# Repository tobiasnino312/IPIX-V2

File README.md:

# IPIX-V2
Robot seguidor de línea utilizado desde el 30/08/2025 en el interzonal de Trelew de la LNR argentina con un 3° puesto interzonal. 
El mismo trabaja con el microcontrolador Arduino Nano, TB6612FNG, motores ProFast de 4000rpm, una bateria LiPo 4s 600mAh armada casera, llantas y cubiertas JSUMO SLT20 y una regleta de sensores QTR8A genérica, similar a la de Pololu. 
Posee un switch DIP para selección de estrategias o configuraciones (empleado para cambio de velocidad según interior o exterior de la pista) y una programación basada en PID básico. 
En cuanto al código, se probó un sistema con intervalos de tiempo para el control dinámico de velocidades base/máximas o parámetros de cálculo del PID, pero debido al poco tiempo de pruebas en pista no se pudo aprovechar. Además, se está desarrollando un algoritmo con Twiddle (un algoritmo de tuning de PID con una especie de aprendizaje escalonado muy básico) que aún no fue probado en pista, con el objetivo de optimizar el tiempo de pruebas en competencia y recopilar datos de tiempo de vuelta y constantes del cálculo del PID.
Por otro lado, se está avanzando con el diseño de una tercera versión (IPIX V3) migrando a una BluePill (STM32F103C8T6), RZ7899 como drivers de motores, hueco para una turbina para mayor adherencia (la limitante actual del prototipo) y 10 sensores QRE1113 directamente soldados a placa con lectura directa por cada canal del ADC disponible.

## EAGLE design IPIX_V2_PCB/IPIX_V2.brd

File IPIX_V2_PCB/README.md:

Todos los diseños realizados en esta segunda versión del robot fueron realizados en Eagle 7.6.0

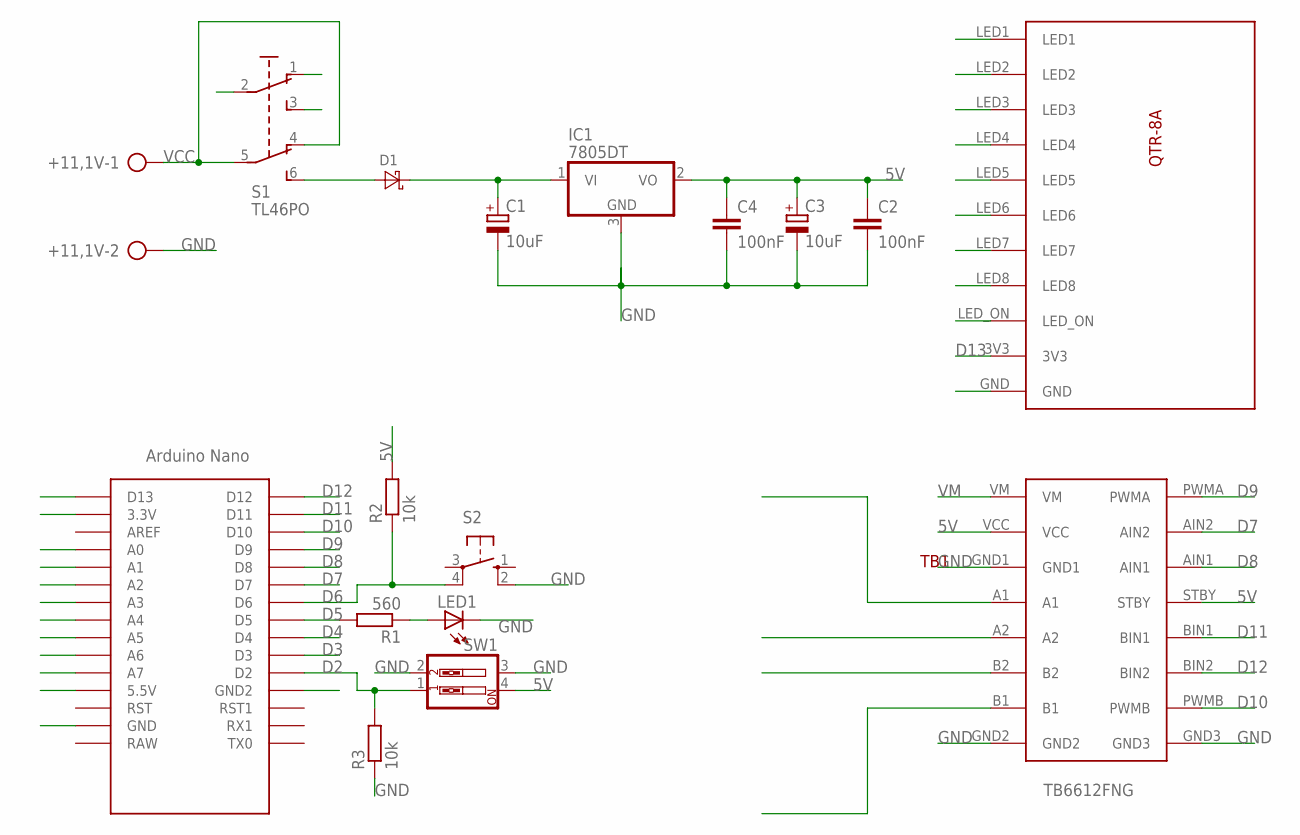
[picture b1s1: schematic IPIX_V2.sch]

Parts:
+11,1V: AK500/2-H
C1, C3: 10uF; E2,5-6E
C2, C4: 100nF; C0805
D1: DIODE-SCHOTTKY-DO201AD; DO201AD
IC1: 7805DT; TO252
LED1: LED3MM
R1: 560; 0204/7
R2, R3: 10k; R0805
S1: TL46PO; TL4XPO
S2: 10-XX; B3F-10XX
SW1: SW_DIP-2; EDG-02
TB1: TB6612FNG
U$1: NANO
U$2: QTR-8A

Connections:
3,3V: U$1.3.3V
5V: C2.1, C3.+, C4.1, IC1.2 (VO), R2.2, SW1.4, TB1.STBY, TB1.VCC, U$1.5V (5.5V), U$2.LED8
A0: U$1.A0, U$2.LED_ON
A1: U$1.A1, U$2.LED1
A2: U$1.A2, U$2.LED2
A3: U$1.A3, U$2.LED3
A4: U$1.A4, U$2.LED4
A5: U$1.A5, U$2.LED5
A6: U$1.A6, U$2.LED6
A7: U$1.A7, U$2.LED7
D2: R3.2, SW1.1, U$1.D2
D3: U$1.D3
D4: U$1.D4
D5: R1.2, U$1.D5
D6: R2.1, S2.4 (P1), U$1.D6
D7: TB1.AIN2, U$1.D7
D8: TB1.AIN1, U$1.D8
D9: TB1.PWMA, U$1.D9
D10: TB1.PWMB, U$1.D10
D11: TB1.BIN1, U$1.D11
D12: TB1.BIN2, U$1.D12
D13: U$1.D13, U$2.3V3
GND: +11,1V.2, C1.-, C2.2, C3.-, C4.2, IC1.3 (GND), LED1.K (C), R3.1, S1.1 (O), S1.2, S1.3 (S), S2.2 (S1), SW1.2, SW1.3, TB1.GND1, TB1.GND2, TB1.GND3, U$1.GND, U$1.GND1 (GND2), U$2.GND
unnamed: D1.A, S1.6 (S1)
unnamed 24: TB1.A2; also elsewhere on the board
unnamed 25: TB1.A1; also elsewhere on the board
unnamed: LED1.A, R1.1
unnamed 42: TB1.B2; also elsewhere on the board
unnamed 43: TB1.B1; also elsewhere on the board
VCC: +11,1V.1, S1.4 (O1), S1.5 (P1)
VM: C1.+, D1.C, IC1.1 (VI), TB1.VM

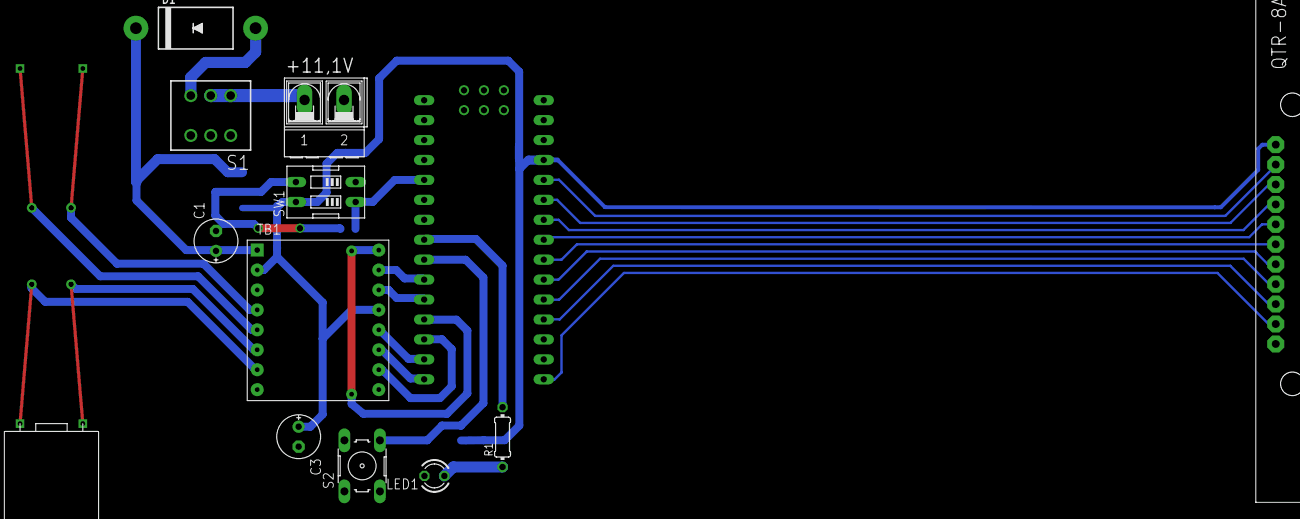
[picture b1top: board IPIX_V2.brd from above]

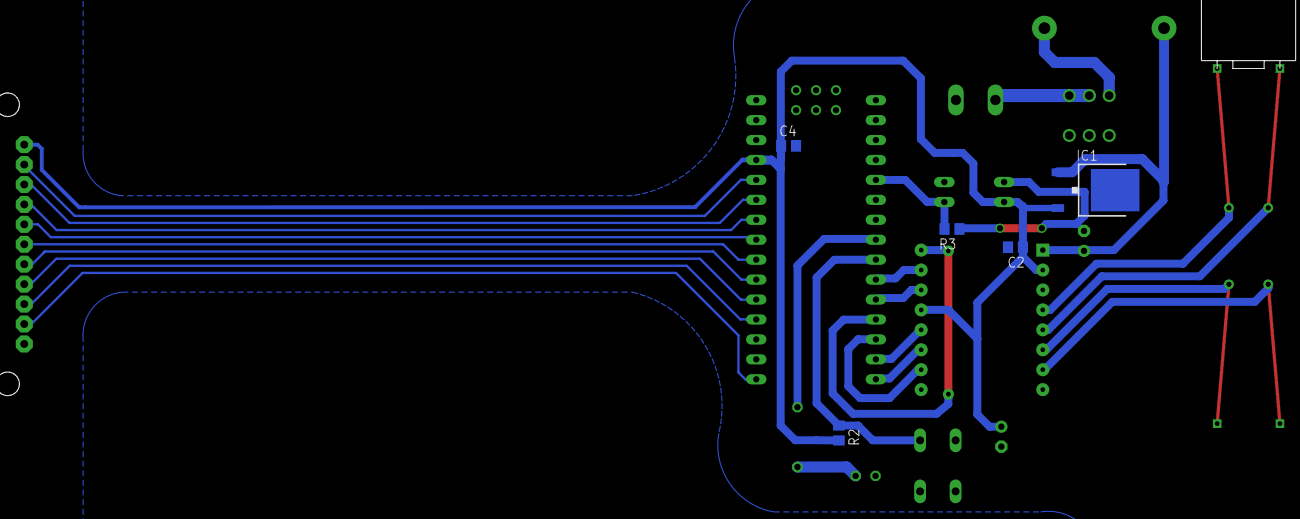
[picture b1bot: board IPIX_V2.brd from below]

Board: 2 copper layers, 19 parts (6 on the bottom side), 28 nets.

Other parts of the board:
U$3, U$4: MOTOR_N20

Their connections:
unnamed 24: U$3.M2; also elsewhere on the board
unnamed 25: U$3.M1; also elsewhere on the board
unnamed 42: U$4.M1; also elsewhere on the board
unnamed 43: U$4.M2; also elsewhere on the board

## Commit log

2026-02-18 README.md
